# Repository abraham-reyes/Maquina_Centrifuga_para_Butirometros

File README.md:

# Proyecto_Maquina_Centrifuga_para_Butirometros

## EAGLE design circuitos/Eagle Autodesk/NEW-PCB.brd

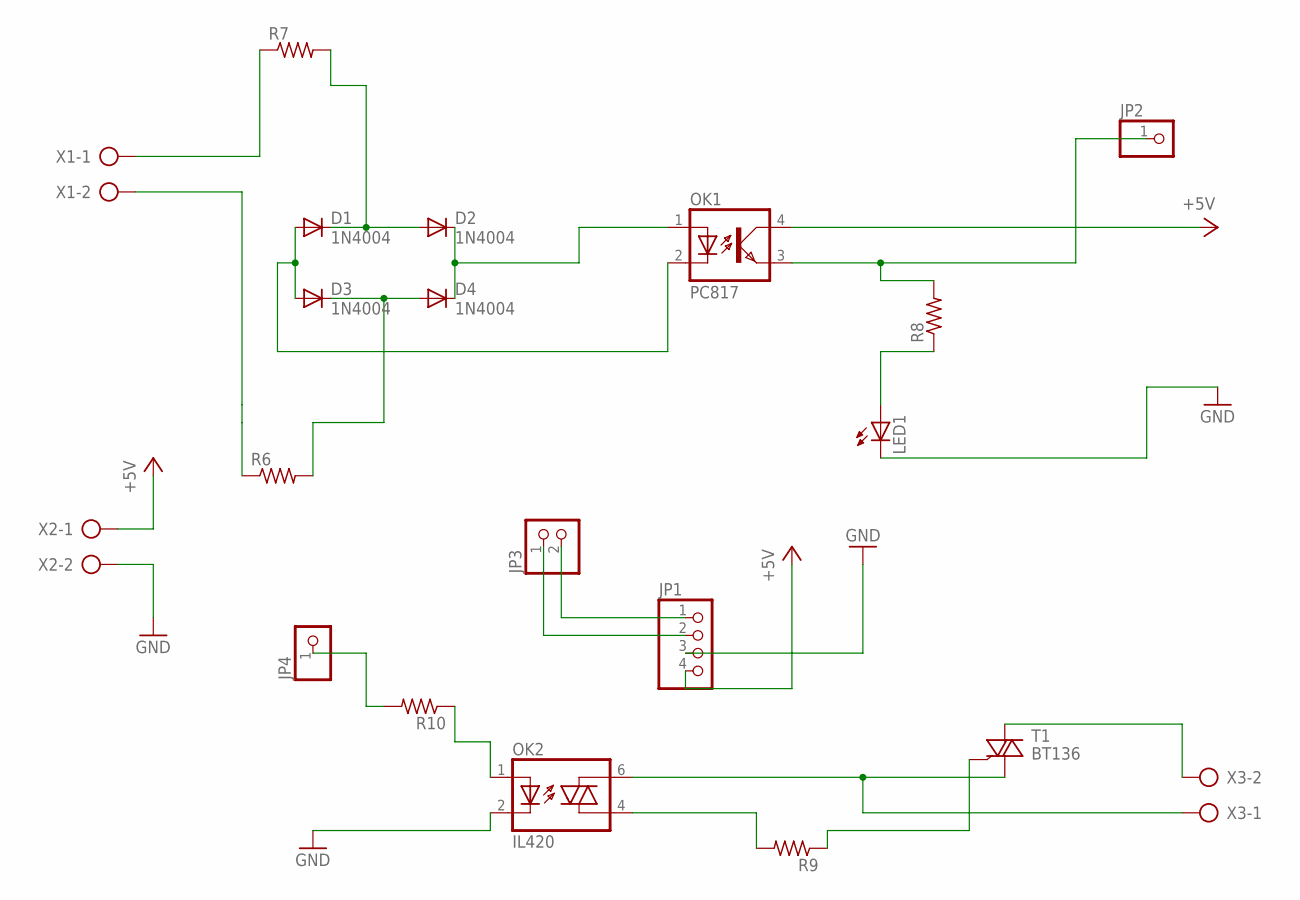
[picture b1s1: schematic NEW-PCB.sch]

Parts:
D1, D2, D3, D4: 1N4004; DO41-10
JP1: PINHD-1X4; 1X04
JP2, JP4: PINHD-1X1; 1X01
JP3: PINHD-1X2; 1X02
LED1: LED5MM
OK1: PC817; DIL04
OK2: IL420; DIL06
R6, R7, R8, R9, R10: R-US_0411/15; 0411/15
T1: BT136; TO220AB
X1, X2, X3: AK300/2

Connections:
+5V: JP1.4, OK1.4 (COL), X2.1
GND: JP1.3, LED1.K (C), OK2.2 (C), X2.2
unnamed: R7.1, X1.1
unnamed: R6.1, X1.2
unnamed: D3.C, D4.A, R6.2
unnamed: D1.C, D2.A, R7.2
unnamed: D1.A, D3.A, OK1.2 (C)
unnamed: D2.C, D4.C, OK1.1 (A)
unnamed: JP1.1, JP3.2
unnamed: LED1.A, R8.1
unnamed: JP2.1, OK1.3 (EMIT), R8.2
unnamed: JP1.2, JP3.1
unnamed: JP4.1, R10.2
unnamed: OK2.1 (A), R10.1
unnamed: OK2.6 (A2), T1.1 (A1), X3.1
unnamed: T1.2 (A2), X3.2
unnamed: OK2.4 (A1), R9.2
unnamed: R9.1, T1.3 (G)

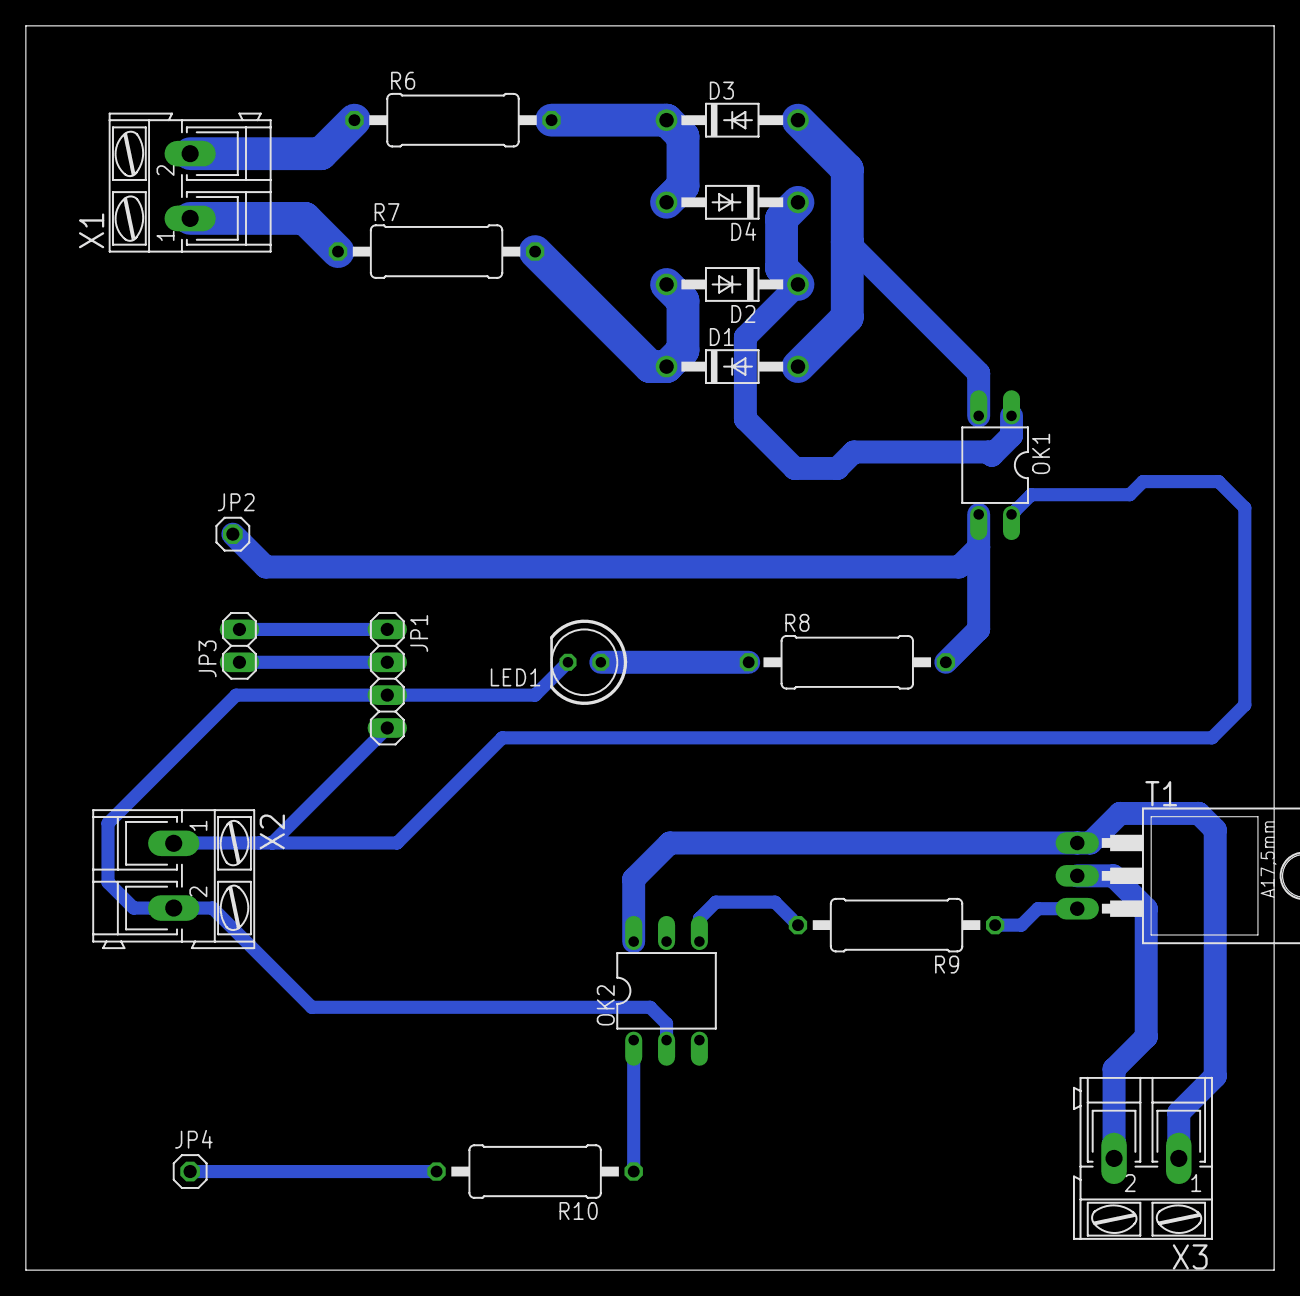
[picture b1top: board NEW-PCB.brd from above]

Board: 2 copper layers, 96.5 x 96.2 mm, 20 parts (0 on the bottom side), 18 nets.

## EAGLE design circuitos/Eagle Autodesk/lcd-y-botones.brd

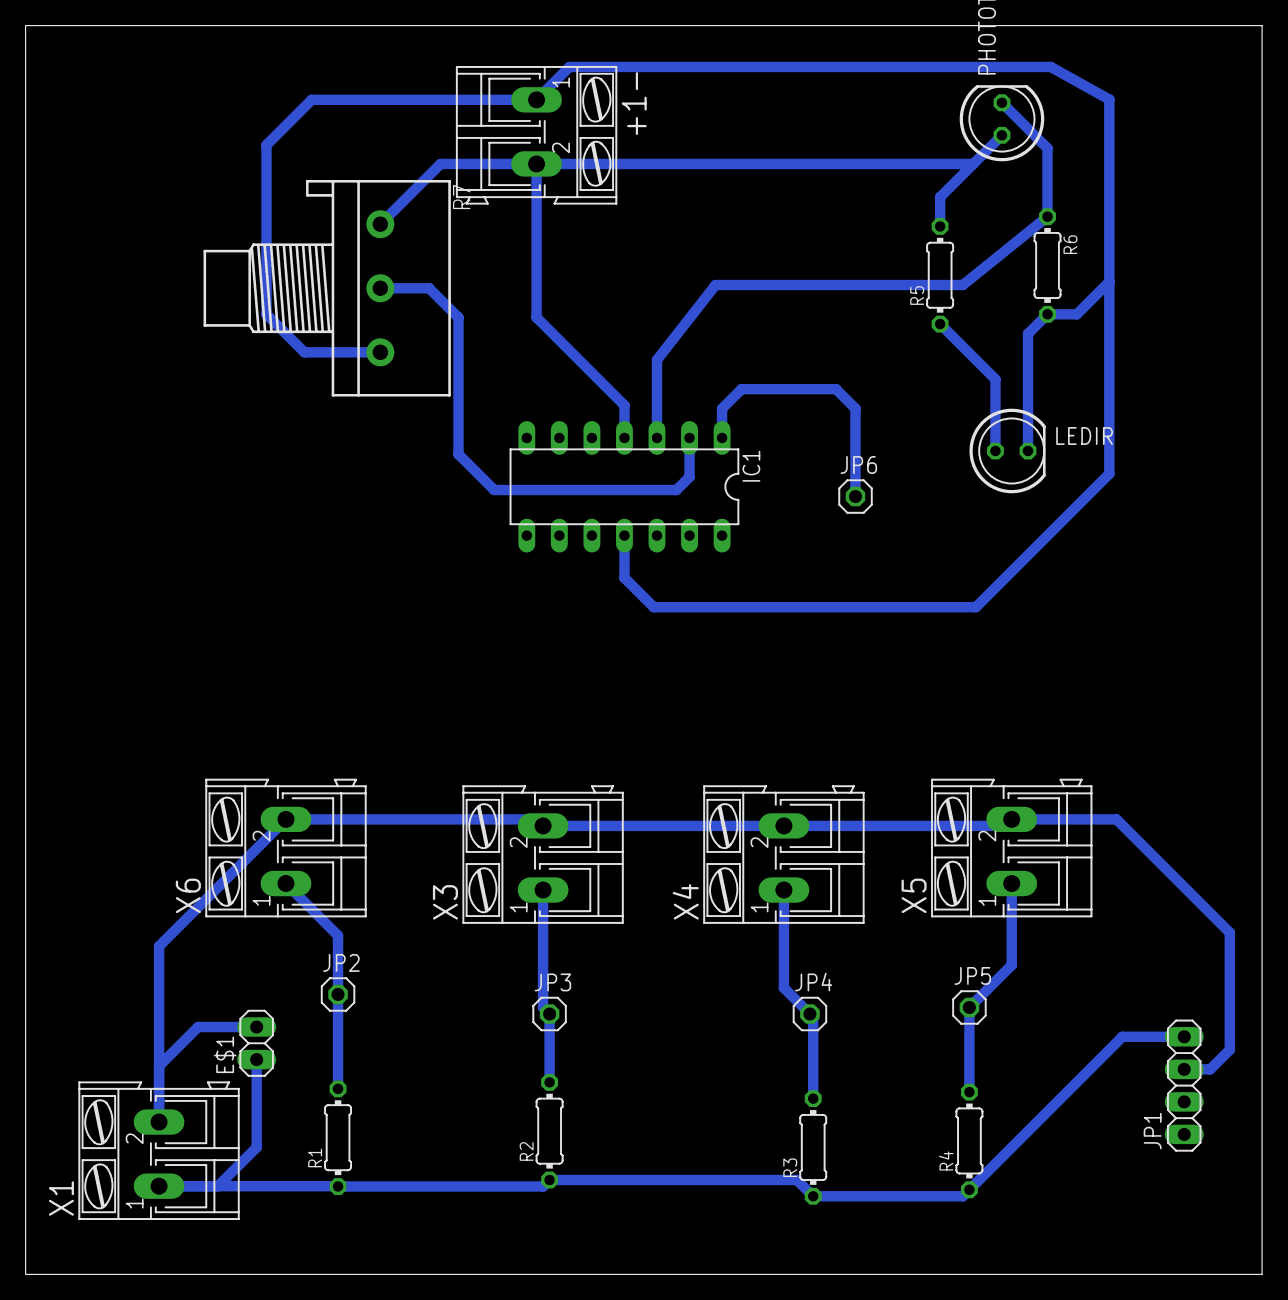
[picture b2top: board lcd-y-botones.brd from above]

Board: 2 copper layers, 96.5 x 97.5 mm, 23 parts (0 on the bottom side), 12 nets.

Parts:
+1-: AK300/2
E$1: 1X02
IC1: LM324N; DIL14
JP1: 1X04
JP2, JP3, JP4, JP5, JP6: 1X01
LEDIR: LED5MM
PHOTOTRANSIOTR: LED5MM
R1, R2, R3, R4: 0204/7
R5: 100; 0204/7
R6: 4.7k; 0204/7
R7: 3RP/1610N
X1, X3, X4, X5, X6: AK300/2

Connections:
unnamed: JP1.3, X1.2, X3.2, X4.2, X5.2, X6.2
unnamed: JP1.4, R1.1, R2.1, R3.1, R4.1, X1.1
unnamed: JP5.1, R4.2, X5.1
unnamed: JP4.1, R3.2, X4.1
unnamed: JP3.1, R2.2, X3.1
unnamed: JP2.1, R1.2, X6.1
unnamed: +1-.2, PHOTOTRANSIOTR.A, R5.2, R7.1
unnamed: LEDIR.A, R5.1
unnamed: +1-.1, LEDIR.K, R6.2, R7.3
unnamed: IC1.2, R7.2
unnamed: IC1.1, JP6.1
unnamed: IC1.3, PHOTOTRANSIOTR.K, R6.1

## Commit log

2020-05-27 Circuits
    Circuitos de la centrifuga
2020-05-27 Documentación
    Documentacion del proyecto
2020-05-27 Programación
    Programación de la centrifuga
2020-05-27 Diseño
    Diseño en AutoCad
2020-05-27 Extras
    Mas herramientas usadas en el desarrollo del proyecto
2020-05-28 Bienvenida
    Datos sobre el Proyecto
2020-05-28 Diseño
    Diseño en SW Y AUTOCAD
2020-06-02 Create Bienvenida
2020-06-02 Revert "Delete Bienvenida"
    This reverts commit ea62d2f0c595b6f6007338ad2d748bd2e1d038e3.
2020-06-02 Revert "Revert "Delete Bienvenida""
    This reverts commit ed3232ea1cf2901eae3bb4990e2a8237673b289e.
2020-06-02 Bienvenida
2020-06-02 Programacion Digital
2020-06-02 Extras
2020-06-02 Eagle
